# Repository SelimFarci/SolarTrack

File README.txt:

# **********************************    Projet S7/S8 - Générateur autoporté 600W    **********************************
À terme, ce générateur de réseau local indépendant 230V-50Hz pourra non seulement être piloté à l'aide d'une télécommande radio, mais aussi suivre le soleil en continu, maximisant la production du panneau photovoltaïque.
## 🔧 ## 🔧 Mes contributions principales dans ce projet :
- Motorisation du dispositif (Avancer, Reculer, Tourner à droite, Tourner à gauche) depuis une manette radio.
- Contrôle de l’orientation du panneau photovoltaïque « face au soleil »
### 👨‍🏫 ### 👨‍🏫 Encadrant :
- Mr TOUSSAINT
### 🧑‍🔧 ### 🧑‍🔧 Intervenants :
- Mme KITTEL (Plateau Technique)  
- Mr LE BIDAN (Atelier Mécanique)  
- Mr BENOITON (Plateau Technique)
### 🤝 ### 🤝 Collaborateurs :
- Sai DAS  
- Rayen BEN AMAR  
- Sélim FARCI  
- Benjamin WYSOCKI  
- Vincent LAKHMECHE  
- Jauffrey FOUKOU GOUAKA  
- Jérémy TOTO
> > Réalisé par des étudiants en 2ème année à l'ENSEA.
---
## 📸 Photos du projet :
<p align="center">

</p>

---

## 📸 Photos du projet :

<p align="center">

</p>

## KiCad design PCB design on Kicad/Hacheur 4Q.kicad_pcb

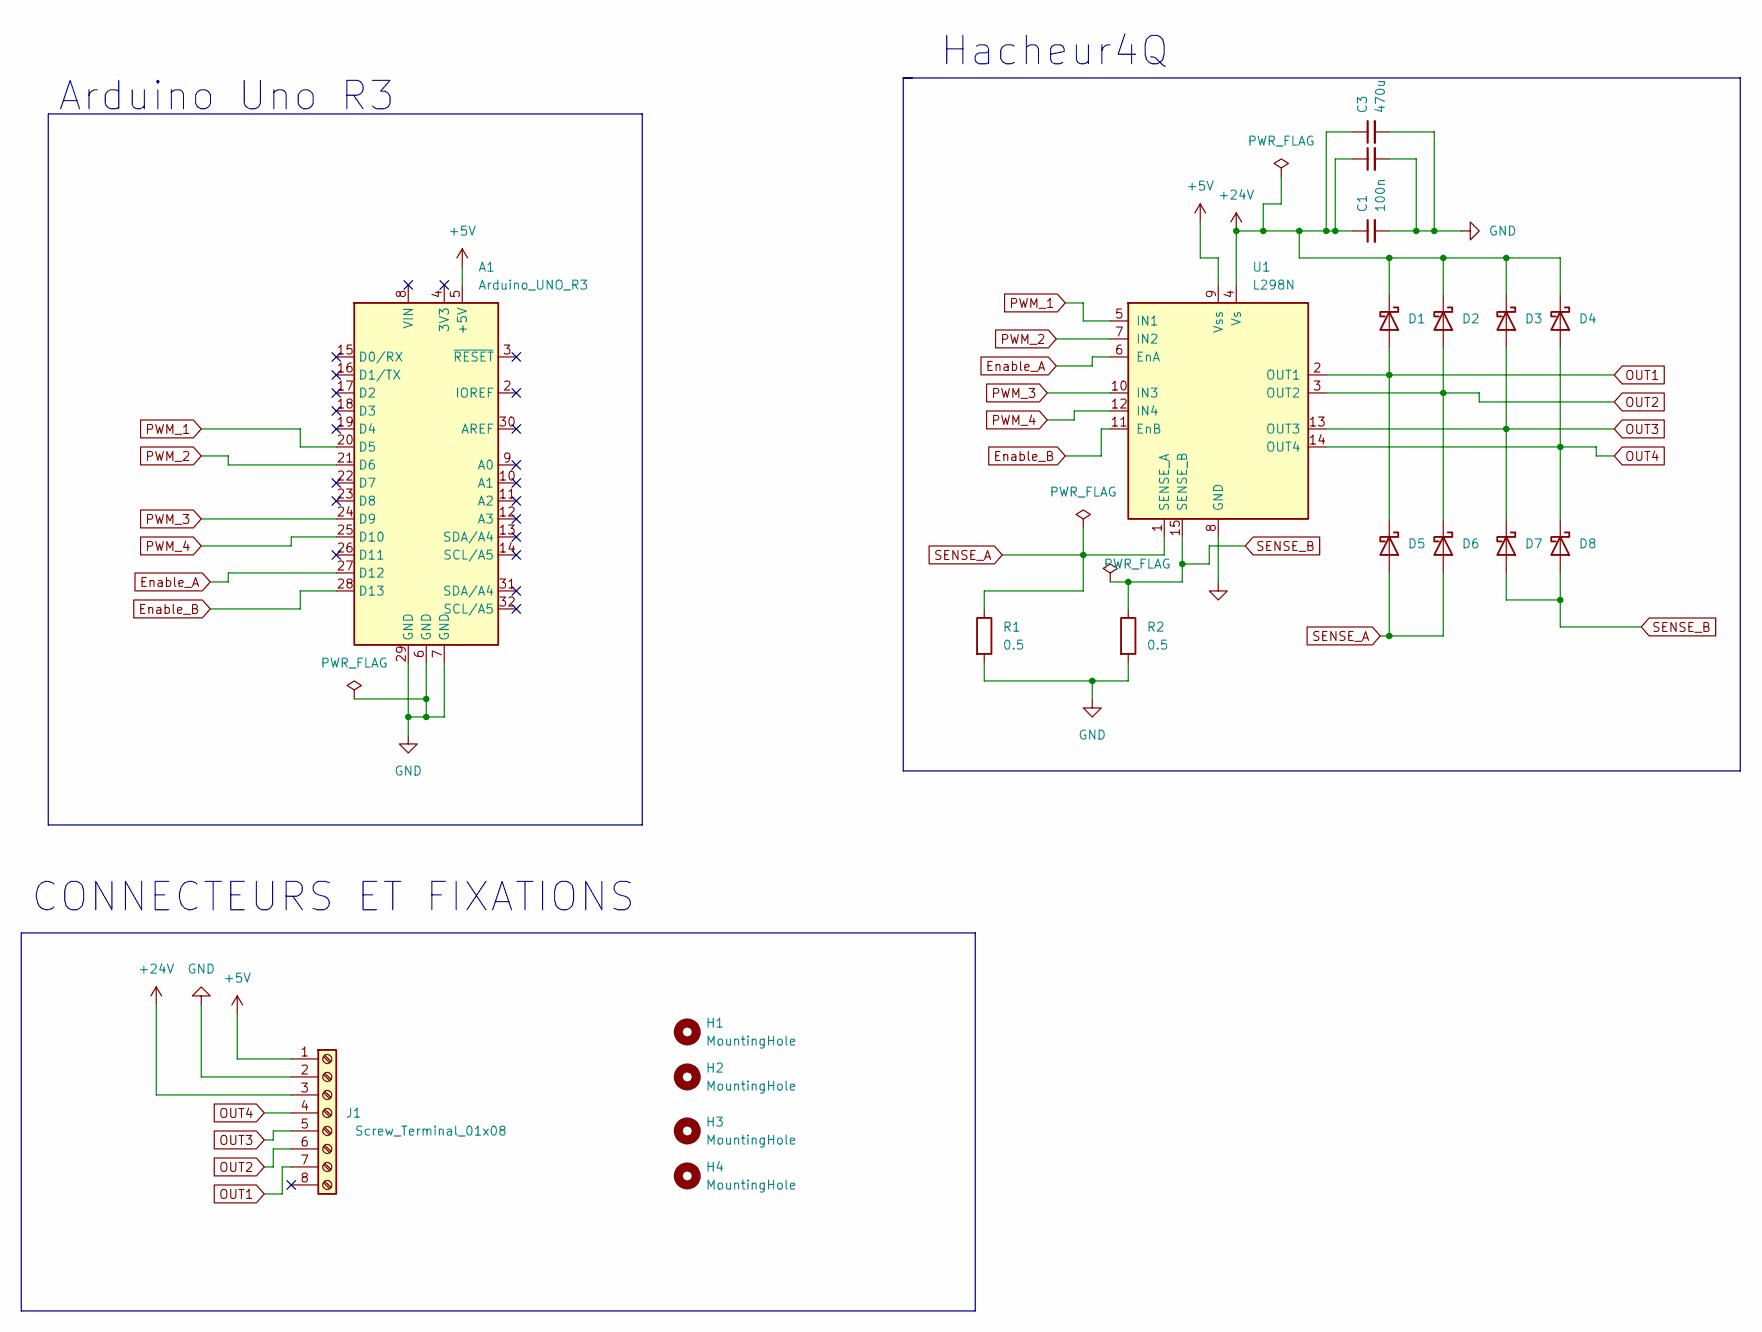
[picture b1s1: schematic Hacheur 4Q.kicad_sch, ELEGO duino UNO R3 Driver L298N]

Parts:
A1: Arduino_UNO_R3
C1: 100n; CP_Radial_D5.0mm_P2.00mm
C2, C3: 470u; CP_Radial_D8.0mm_P3.50mm
D1, D2, D3, D4, D5, D6, D7, D8: B120-E3; D_SMA
H1, H2, H3, H4: MountingHole; MountingHole_3.2mm_M3
J1: Screw_Terminal_01x08; TerminalBlock_Phoenix_MKDS-1,5-8-5.08_1x08_P5.08mm_Horizont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
R1, R2: 0.5; R_2512_6332Metric_Pad1.40x3.35mm_HandSolder
U1: L298N; TO-220-15_P2.54x2.54mm_StaggerOdd_Lead4.58mm_Vertical

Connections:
+5V: A1.5 (+5V), J1.1, U1.9 (Vss)
+24V: C1.1, C2.1, C3.1, D1.1 (K), D2.1 (K), D3.1 (K), D4.1 (K), J1.3, U1.4 (Vs)
Enable_A: A1.27 (D12), U1.6 (EnA)
Enable_B: A1.28 (D13), U1.11 (EnB)
GND: A1.6 (GND), A1.7 (GND), A1.29 (GND), C1.2, C2.2, C3.2, J1.2, R1.2, R2.2, U1.8 (GND)
OUT1: D1.2 (A), D5.1 (K), J1.7, U1.2 (OUT1)
OUT2: D2.2 (A), D6.1 (K), J1.6, U1.3 (OUT2)
OUT3: D3.2 (A), D7.1 (K), J1.5, U1.13 (OUT3)
OUT4: D4.2 (A), D8.1 (K), J1.4, U1.14 (OUT4)
PWM_1: A1.20 (D5), U1.5 (IN1)
PWM_2: A1.21 (D6), U1.7 (IN2)
PWM_3: A1.24 (D9), U1.10 (IN3)
PWM_4: A1.25 (D10), U1.12 (IN4)
SENSE_A: D5.2 (A), D6.2 (A), R1.1, U1.1 (SENSE_A)
SENSE_B: D7.2 (A), D8.2 (A), R2.1, U1.15 (SENSE_B)

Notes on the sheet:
Hacheur4Q
Arduino Uno R3
CONNECTEURS ET FIXATIONS

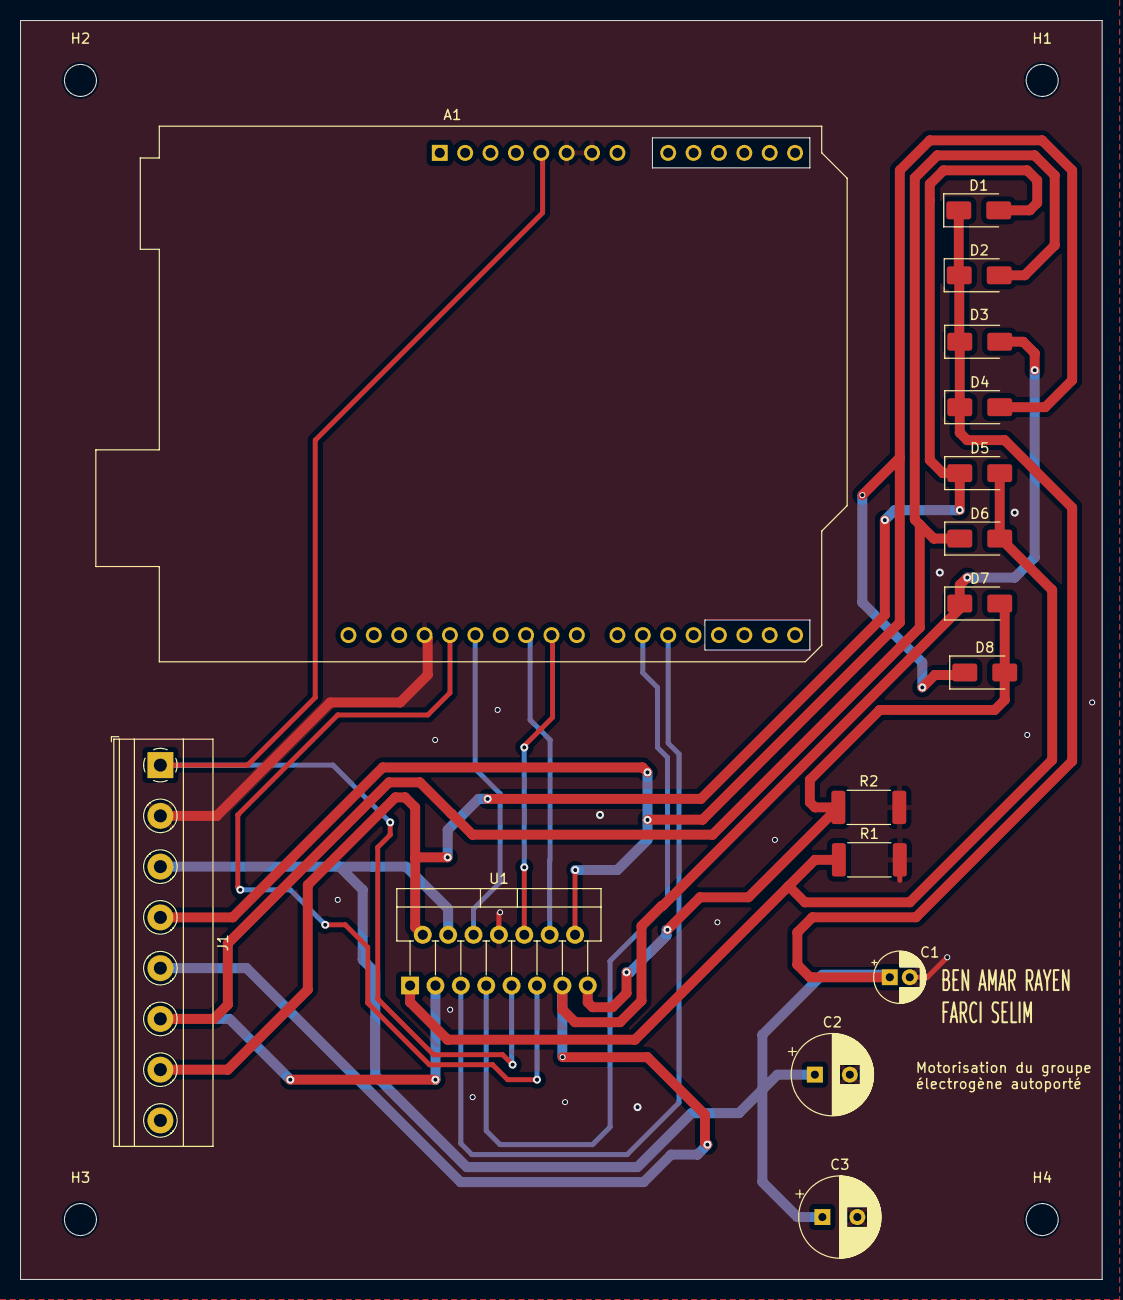
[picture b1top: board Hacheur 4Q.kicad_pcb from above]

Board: 2 copper layers, 108.2 x 126.0 mm, 20 parts (0 on the bottom side), 15 nets.
